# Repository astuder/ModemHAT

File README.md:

# Modem HAT for the Raspberry Pi

This HAT is a modem that connects the Raspberry Pi to a plain old analog telephone line.

The modem presents itself to the Raspberry Pi on an UART and is controlled with the classic AT command set. It supports various standards (V.22bis, V.32bis, V.34, V.90, ...) at speeds of up to 56 kbps.

The design is based on a [Skyworks ISOmodem](https://www.skyworksinc.com/en/Products/Modems-and-DAAs/Data-and-Voice-Modems) chipset, specifically [Si2457](https://www.skyworksinc.com/en/Products/Modems-and-DAAs/Data-and-Voice-Modems/Si2457) data modem and Si3018 line side driver. The implementation
closely follows the circuits described in application note [AN93](https://www.skyworksinc.com/-/media/SkyWorks/SL/documents/public/application-notes/AN93.pdf).

The Modem HAT was successfully tested on the [Shadytel](https://shady.tel/) phone network at Toorcamp 2022.

> [!CAUTION]
> Whatever your jurisdiction, we're pretty positive that connecting this device to the public phone system IS NOT LEGAL! Don't blame us if you get into trouble.

## Raspberry Pi Configuration

> [!NOTE]
> This information was tested on Raspberry Pi 4 and Raspberry 5, running Raspberry Pi OS 12 (Bookworm). There may be differences for other versions of the Pi and/or Pi OS.

The modem HAT requires a Raspberry Pi 4 or newer.

The modem communicates through the Pi's UART on GPIO 8-11, and requires CTS and RTS for flow control. The modem supports automatic baudrate detection at speeds up to 307.2 kps.

Before first use after power-up, the modem needs to be reset. To reset the modem, GPIO25 (pin 22) is set low for at least 500ms, then set high, followed by a delay of at least 300ms. 

By default, the modem is configured for operation in the United States. For other countries the modem may have to be reconfigured after reset. See [AN93](https://www.skyworksinc.com/-/media/SkyWorks/SL/documents/public/application-notes/AN93.pdf) chapter 6.2 for details. 

Below are the configuration steps for Raspberry Pi 4 and Raspberry Pi 5.

### Raspberry Pi 4

To enable the UART, edit `/boot/firmware/config.txt` and add the following line at the end of the file:

`dtoverlay=uart4,ctsrts`

After rebooting the Raspberry Pi, the UART is mapped to `/dev/ttyAMA4`.

To reset the modem, run the Python script [`reset-pi4.py`](python/reset-pi4.py).

The modem is now ready to use. For example connect to the modem by running:

`screen /dev/ttyAMA4 115200`

Once connected to the modem, if you type `at` and press enter, the modem should respond with `OK`.

### Raspberry Pi 5

To enable the UART, edit `/boot/firmware/config.txt` and add the following line at the end of the file:

`dtoverlay=uart3-pi5,ctsrts`

After rebooting the Raspberry Pi, the UART is mapped to `/dev/ttyAMA3`.

To reset the modem, run the Python script [`reset-pi5.py`](python/reset-pi5.py).

The modem is now ready to use. For example connect to the modem by running:

`screen /dev/ttyAMA3 115200`

Once connected to the modem, if you type `at` and press enter, the modem should respond with `OK`.

## AT Command Set

The modem supports the [basic Hayes command set](https://en.wikipedia.org/wiki/Hayes_command_set#The_basic_Hayes_command_set).

For a complete list of supported AT commands as well as configuration registers refer to [AN93](https://www.skyworksinc.com/-/media/SkyWorks/SL/documents/public/application-notes/AN93.pdf) chapters 5.4 through 5.7. 

## Raspberry Pi GPIO Pinout

Required connections:
|Pin|Description|
|-|-|
|1|3.3V power for modem chipset|
|2,4|5V power for audio amplifier|
|6|GND|
|19|UART CTS|
|21|UART RX|
|22|Modem reset, RPi GPIO25|
|23|UART RTS|
|24|UART TX|

Optional connections:
|Pin|Description|
|-|-|
|13|Modem interrupt, RPi GPIO27|
|15|Modem boot config EEPROM SDIO, RPi GPIO22|
|16|Modem boot config EEPROM CS, RPi GPIO23|
|18|Modem boot config EEPROM CLK, Rpi GPIO24|
|27|RPi config EEPROM SDA|
|28|RPi config EEPROM SCL|

In the standard configuration of the HAT, the modem boot config and interrupt pins are not electrically connected to the Rasbperry Pi GPIO header. Populate R29-R32 with 0-ohm resistors to use these pins.

## Building Your Own HAT

### General

Large parts of the HAT are based on the hardware design reference in application note [AN93](https://www.skyworksinc.com/-/media/SkyWorks/SL/documents/public/application-notes/AN93.pdf) chapter 4. Where applicable, identical component designators are used to simplify cross-referencing. 

I used solder paste, stencil and reflow oven for assembly of the HAT. I also ordered partially assembled boards from JLCPCB, and manually soldered the parts that they didn't have in stock (modem chipset and high-voltage capacitors).

After soldering the through-hole parts (RJ11 connector, speaker), make sure to clip the leads on the bottom side of the HAT to avoid shorting with metal parts on the Raspberry Pi.

### Modem

The modem chipset consists of the digital part Si2457 (U1) and analog part Si3018 (U2).

These are expensive parts, costing US $13-$16 and $6-$8 respectively when purchased from reputable distributors. While tempting, beware of sources like Ebay and AliExpress as parts may be salvaged, old or even fake. It will be much easier to diagnose problems without having to second guess whether the core components of the HAT are genuine.

The HAT uses a 32.768 kHz crystal (Y1) to clock the Si2457, mainly chosen for small size and because I already had a few in my parts bin. The downside of this choice are the slow reset sequence (800 ms) and that this clocking option is only supported by Si2457 revision D (part number SI2457-D-FT) or newer.

If you suspect that you're stuck with an old part, you could try using a 4.9152 MHz crystal instead. In that case you must remove R17 which configures the clock speed. You may also have to replace the load capacitors (C40, C41) with appropriate values. See [AN93](https://www.skyworksinc.com/-/media/SkyWorks/SL/documents/public/application-notes/AN93.pdf) chapter 4.1.3 for details.

On the analog side, most of the resistors, capacitors, diodes and transistors have critical voltage, current and/or power ratings. These are all called out in the schematic. See bill of material in [AN93](https://www.skyworksinc.com/-/media/SkyWorks/SL/documents/public/application-notes/AN93.pdf) chapter 4.3 for full details. 

For bring-up and troubleshooting of the modem portion of the circuit, refer to [AN93](https://www.skyworksinc.com/-/media/SkyWorks/SL/documents/public/application-notes/AN93.pdf) chapter 10.1. 

### Audio Output / Speaker

The audio output is optional and allows monitoring of connection progress via a speaker, and who doesn't love the old-school sounds of two dial-up modems negotiating a session. It's half the reason to build this project! :)

The audio amplifier LM4819 (U4) can be substituted with the higher power, pin-compatible LM4862. Cheap, off-brand substitutes are probably fine too.

The HAT has a footprint for a 15mm speaker, like for example CUI Devices CVS-1508. Alternatively, footprint J3 provides connectivity via a JST-PH connector, or directly soldering speaker wires to the pads.

If audio is not needed, the audio amplifier (U4) and associated parts (C12-C19, R19-R24, SW1, J3) can be left unpopulated.

To enable audio output on the speaker, make sure MUTE switch is set towards the LEDs. The AT command to enable speaker output while dialing and handshaking is `ATM1`. Speaker volume is controlled with `ATL1` through `ATL4`, where 4 is the loudest.

### Modem Boot Config EEPROM

The modem boot config EEPROM is optional and can store AT commands that the modem automatically runs after reset. See [AN93](https://www.skyworksinc.com/-/media/SkyWorks/SL/documents/public/application-notes/AN93.pdf) chapter 2.7 for details.

The EEPROM can be programmed by the modem with AT commands. For hacking, the EEPROM can also be connected to the Raspberry Pi by populating R29, R30 and R31. For the latter, keep the modem in reset while interacting with the EEPROM.

If this functionality is not needed, the EEPROM (U6) and associated parts (C22, R26, R27, R28) can be left unpopulated.

### Raspberry Pi HAT ID EEPROM

The HAT ID EEPROM is optional and can store information that allows the Raspberry Pi to recognize the HAT and load the required device tree overlay, i.e. automatically configure UART and other pins.

I haven't figured out the content for this EEPROM yet. Specification is [here](https://github.com/raspberrypi/hats/blob/master/eeprom-format.md). Contributions are welcome :)

If this functionality is not needed, the EEPROM (U5) and associated parts (C21, R14, R25) can be left unpopulated.

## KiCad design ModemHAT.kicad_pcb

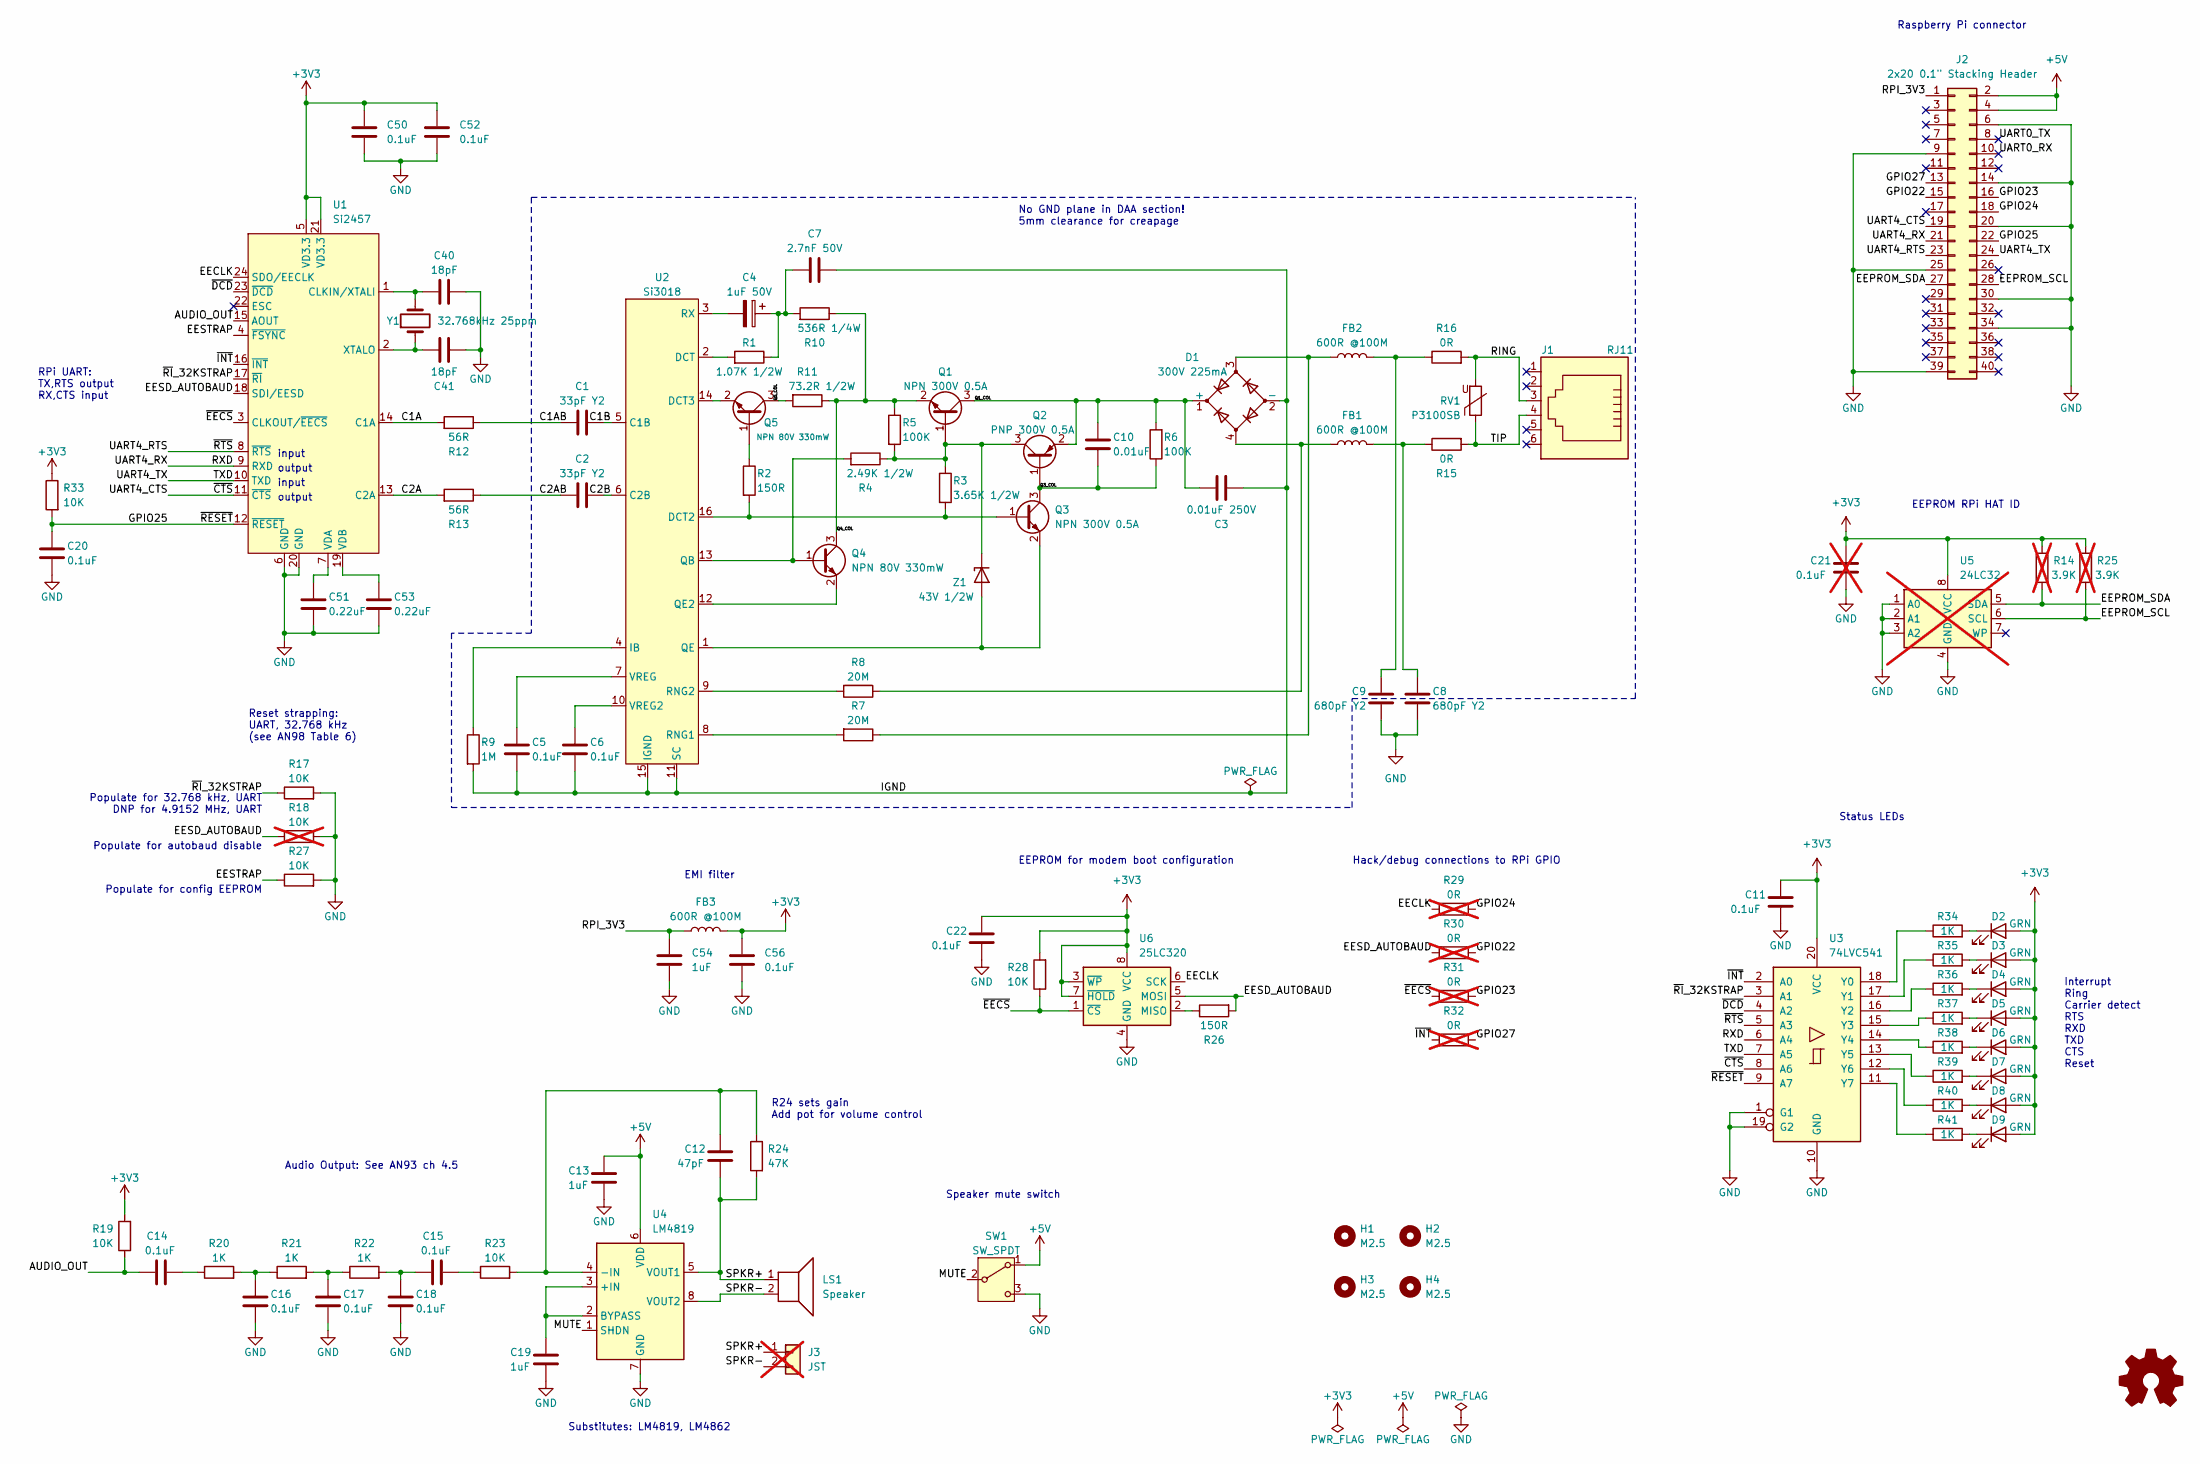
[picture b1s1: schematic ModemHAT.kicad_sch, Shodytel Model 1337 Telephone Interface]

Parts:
C1, C2: 33pF Y2; C_1808_4520Metric; MPN SCC1808N330J502TG
C3: 0.01uF 250V; C_0805_2012Metric; MPN GRM21BR72E103KW03L
C4: 1uF 50V; CP_Elec_4x5.4; LCSC C371267
C5, C6, C11, C14, C15, C16, C17, C18, C20, C22, C50, C52, C56: 0.1uF; C_0603_1608Metric; LCSC C14663
C7: 2.7nF 50V; C_0603_1608Metric; LCSC C1609
C8, C9: 680pF Y2; C_1808_4520Metric; MPN 502R29W681KV3E-****-SC
C10: 0.01uF; C_0603_1608Metric; LCSC C57112
C12: 47pF; C_0603_1608Metric; LCSC C1671
C13, C19, C54: 1uF; C_0603_1608Metric; LCSC C15849
C21: 0.1uF; C_0603_1608Metric; LCSC C14663; not fitted
C40, C41: 18pF; C_0603_1608Metric; LCSC C1647
C51, C53: 0.22uF; C_0603_1608Metric; LCSC C21120
D1: 300V 225mA; TO-269AA-R; MPN MB4S-TP; LCSC C151727
D2, D3, D4, D5, D6, D7, D8, D9: GRN; LED_0805_2012Metric; LCSC C2297
FB1, FB2, FB3: 600R @100M; L_0603_1608Metric; MPN BLM18AG601SN1D; LCSC C1002
H1, H2, H3, H4: M2.5; MountingHole_2.7mm_M2.5
J1: RJ11; RJ12_Amphenol_54601-x06_Horizontal; MPN 54601-906001WPLF
J2: 2x20 0.1" Stacking Header; Raspberry_Pi_Stacking_Header; LCSC C2685112
J3: JST; JST_PH_B2B-PH-K_1x02_P2.00mm_Vertical; not fitted
LS1: Speaker; Buzzer_15x7.5RM7.6; MPN CVS-1508
Q1, Q3: NPN 300V 0.5A; SOT-23; MPN MMBTA42; LCSC C20069138
Q2: PNP 300V 0.5A; SOT-23; MPN MMBTA92; LCSC C20069146
Q4, Q5: NPN 80V 330mW; SOT-323_SC-70; MPN MMBTA06W; LCSC C268584
R1: 1.07K 1/2W; R_1210_3225Metric; LCSC C333114
R2, R26: 150R; R_0603_1608Metric; LCSC C22808
R3: 3.65K 1/2W; R_1210_3225Metric; LCSC C230230
R4: 2.49K 1/2W; R_1210_3225Metric; LCSC C705453
R5, R6: 100K; R_0603_1608Metric; LCSC C25803
R7, R8: 20M; R_1206_3216Metric; LCSC C384452
R9: 1M; R_0603_1608Metric; LCSC C22935
R10: 536R 1/4W; R_1206_3216Metric; LCSC C364152
R11: 73.2R 1/2W; R_1210_3225Metric; LCSC C2991291
R12, R13: 56R; R_0603_1608Metric; LCSC C25196
R14, R25: 3.9K; R_0603_1608Metric; LCSC C23018; not fitted
R15, R16: 0R; R_0603_1608Metric; LCSC C21189
R17, R19, R23, R27, R28, R33: 10K; R_0603_1608Metric; LCSC C25804
R18: 10K; R_0603_1608Metric; LCSC C25804; not fitted
R20, R21, R22, R34, R35, R36, R37, R38, R39, R40, R41: 1K; R_0603_1608Metric; LCSC C21190
R24: 47K; R_0603_1608Metric; LCSC C25819
R29, R30, R31, R32: 0R; R_0603_1608Metric; LCSC C25819; not fitted
RV1: P3100SB; D_SMB; MPN P3100SBLRP; LCSC C3012560
SW1: SW_SPDT; SW_SPDT_CK_JS102011SAQN; MPN JS102011SAQN; LCSC C221660
U1: Si2457; TSSOP-24_4.4x7.8mm_P0.65mm; MPN Si2457-D-FT
U2: Si3018; SOIC-16_3.9x9.9mm_P1.27mm; MPN Si3018-F-GS
U3: 74LVC541; TSSOP-20_4.4x6.5mm_P0.65mm; LCSC C5657
U4: LM4819; SOIC-8_3.9x4.9mm_P1.27mm; MPN LM4819MX/NOPB; LCSC C87265
U5: 24LC32; TSSOP-8_4.4x3mm_P0.65mm; MPN CAT24C32YI-GT3; not fitted
U6: 25LC320; TSSOP-8_4.4x3mm_P0.65mm; MPN 25LC320AT-I/ST; LCSC C2061659
Y1: 32.768kHz 25ppm; Crystal_SMD_3215-2Pin_3.2x1.5mm; MPN ECS-.327-12.5-34B-TR; LCSC C32346
Z1: 43V 1/2W; D_SOD-123; MPN MMSZ5260BT1G; LCSC C6909653

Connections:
+3V3: C11.1, C21.1, C22.1, C50.2, C52.2, C56.2, D2.2 (A), D3.2 (A), D4.2 (A), D5.2 (A), D6.2 (A), D7.2 (A), D8.2 (A), D9.2 (A), FB3.2, R14.1, R19.2, R25.1, R28.2, R33.1, U1.5 (VD3.3), U1.21 (VD3.3), U3.20 (VCC), U5.8 (VCC), U6.3 (~WP), U6.7 (~HOLD), U6.8 (VCC)
+5V: C13.2, J2.2, J2.4, SW1.1 (A), U4.6 (VDD)
/AUDIO_OUT: C14.2, R19.1, U1.15 (AOUT)
/C1A: R12.2, U1.14 (C1A)
/C1AB: C1.1, R12.1
/C1B: C1.2, U2.5 (C1B)
/C2A: R13.2, U1.13 (C2A)
/C2AB: C2.1, R13.1
/C2B: C2.2, U2.6 (C2B)
/EECLK: R29.2, U1.24 (SDO/EECLK), U6.6 (SCK)
/EEPROM_SCL: J2.28, R25.2, U5.6 (SCL)
/EEPROM_SDA: J2.27, R14.2, U5.5 (SDA)
/EESD_AUTOBAUD: R18.1, R26.2, R30.2, U1.18 (SDI/EESD), U6.5 (MOSI)
/EESTRAP: R27.1, U1.4 (~FSYNC)
/GPIO22: J2.15, R30.1
/GPIO23: J2.16, R31.1
/GPIO24: J2.18, R29.1
/GPIO25: C20.2, J2.22, R33.2, U1.12 (~RESET), U3.9 (A7)
/GPIO27: J2.13, R32.1
/IGND: C3.1, C5.2, C6.2, C7.1, D1.2 (-), R9.2, U2.11 (SC), U2.15 (IGND)
/MUTE: SW1.2 (B), U4.1 (SHDN)
/Q1_COL: C3.2, C10.2, D1.1 (+), Q1.3 (C), Q2.2 (E), R6.2
/Q3_COL: C10.1, Q2.1 (B), Q3.3 (C), R6.1
/Q4_COL: Q1.2 (E), Q4.3 (C), R5.1, R10.1, R11.1
/Q5_COL: Q5.3 (C), R11.2
/RING: J1.3, R16.2, RV1.2
/RPI_3V3: C54.2, FB3.1, J2.1
/RXD: J2.21, U1.9 (RXD), U3.6 (A4)
/SPKR+: C12.2, J3.1, LS1.1, R24.2, U4.5 (VOUT1)
/SPKR-: J3.2, LS1.2, U4.8 (VOUT2)
/TIP: J1.4, R15.2, RV1.1
/TXD: J2.24, U1.10 (TXD), U3.7 (A5)
/UART0_RX: J2.10
/UART0_TX: J2.8
/UART4_CTS: J2.19, U1.11 (~CTS), U3.8 (A6)
/UART4_RTS: J2.23, U1.8 (~RTS), U3.5 (A3)
/~DCD: U1.23 (~DCD), U3.4 (A2)
/~EECS: R28.1, R31.2, U1.3 (CLKOUT/~EECS), U6.1 (~CS)
/~INT: R32.2, U1.16 (~INT), U3.2 (A0)
/~RI_32KSTRAP: R17.1, U1.17 (~RI), U3.3 (A1)
GND: C8.2, C9.2, C11.2, C13.1, C16.1, C17.1, C18.1, C19.1, C20.1, C21.2, C22.2, C40.2, C41.2, C50.1, C51.2, C52.1, C53.2, C54.1, C56.1, J2.6, J2.9, J2.14, J2.20, J2.25, J2.30, J2.34, J2.39, R17.2, R18.2, R27.2, SW1.3 (C), U1.6 (GND), U1.20 (GND), U3.1 (G1), U3.10 (GND), U3.19 (G2), U4.7 (GND), U5.1 (A0), U5.2 (A1), U5.3 (A2), U5.4 (GND), U6.4 (GND)
unnamed: C4.1, C7.2, R1.1, R10.2
unnamed: C8.1, FB1.2, R15.1
unnamed: C9.1, FB2.2, R16.1
unnamed: C14.1, R20.1
unnamed: C15.1, R23.1
unnamed: C15.2, C18.2, R22.2
unnamed: C16.2, R20.2, R21.1
unnamed: C17.2, R21.2, R22.1
unnamed: D1.3, FB2.1, R7.1
unnamed: D1.4, FB1.1, R8.1
unnamed: D2.1 (K), R34.2
unnamed: D3.1 (K), R35.2
unnamed: D4.1 (K), R36.2
unnamed: D5.1 (K), R37.2
unnamed: D6.1 (K), R38.2
unnamed: D7.1 (K), R39.2
unnamed: D8.1 (K), R40.2
unnamed: D9.1 (K), R41.2
unnamed: Q1.1 (B), Q2.3 (C), R3.1, R4.1, R5.2, Z1.1 (K)
unnamed: Q3.1 (B), R2.2, R3.2, U2.16 (DCT2)
unnamed: Q3.2 (E), U2.1 (QE), Z1.2 (A)
unnamed: Q4.1 (B), R4.2, U2.13 (QB)
unnamed: Q4.2 (E), U2.12 (QE2)
unnamed: Q5.1 (B), R2.1
unnamed: Q5.2 (E), U2.14 (DCT3)
unnamed: C40.1, U1.1 (CLKIN/XTALI), Y1.2
unnamed: C51.1, U1.7 (VDA)
unnamed: C53.1, U1.19 (VDB)
unnamed: C41.1, U1.2 (XTALO), Y1.1
unnamed: R1.2, U2.2 (DCT)
unnamed: R9.1, U2.4 (IB)
unnamed: R7.2, U2.8 (RNG1)
unnamed: R8.2, U2.9 (RNG2)
unnamed: C4.2, U2.3 (RX)
unnamed: C6.1, U2.10 (VREG2)
unnamed: C5.1, U2.7 (VREG)
unnamed: R34.1, U3.18 (Y0)
unnamed: R35.1, U3.17 (Y1)
unnamed: R36.1, U3.16 (Y2)
unnamed: R37.1, U3.15 (Y3)
unnamed: R38.1, U3.14 (Y4)
unnamed: R39.1, U3.13 (Y5)
unnamed: R40.1, U3.12 (Y6)
unnamed: R41.1, U3.11 (Y7)
unnamed: C19.2, U4.2 (BYPASS), U4.3 (+IN)
unnamed: C12.1, R23.2, R24.1, U4.4 (-IN)
unnamed: R26.1, U6.2 (MISO)

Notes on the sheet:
Audio Output: See AN93 ch 4.5
Reset strapping: UART, 32.768 kHz (see AN98 Table 6)
EEPROM for modem boot configuration
output
Populate for autobaud disable
EMI filter
Interrupt Ring Carrier detect RTS RXD TXD CTS Reset
EEPROM RPi HAT ID
Status LEDs
Populate for 32.768 kHz, UART DNP for 4.9152 MHz, UART
Speaker mute switch
No GND plane in DAA section! 5mm clearance for creapage
Hack/debug connections to RPi GPIO
Populate for config EEPROM
Raspberry Pi connector
R24 sets gain Add pot for volume control
input
Substitutes: LM4819, LM4862
RPi UART: TX,RTS output RX,CTS input

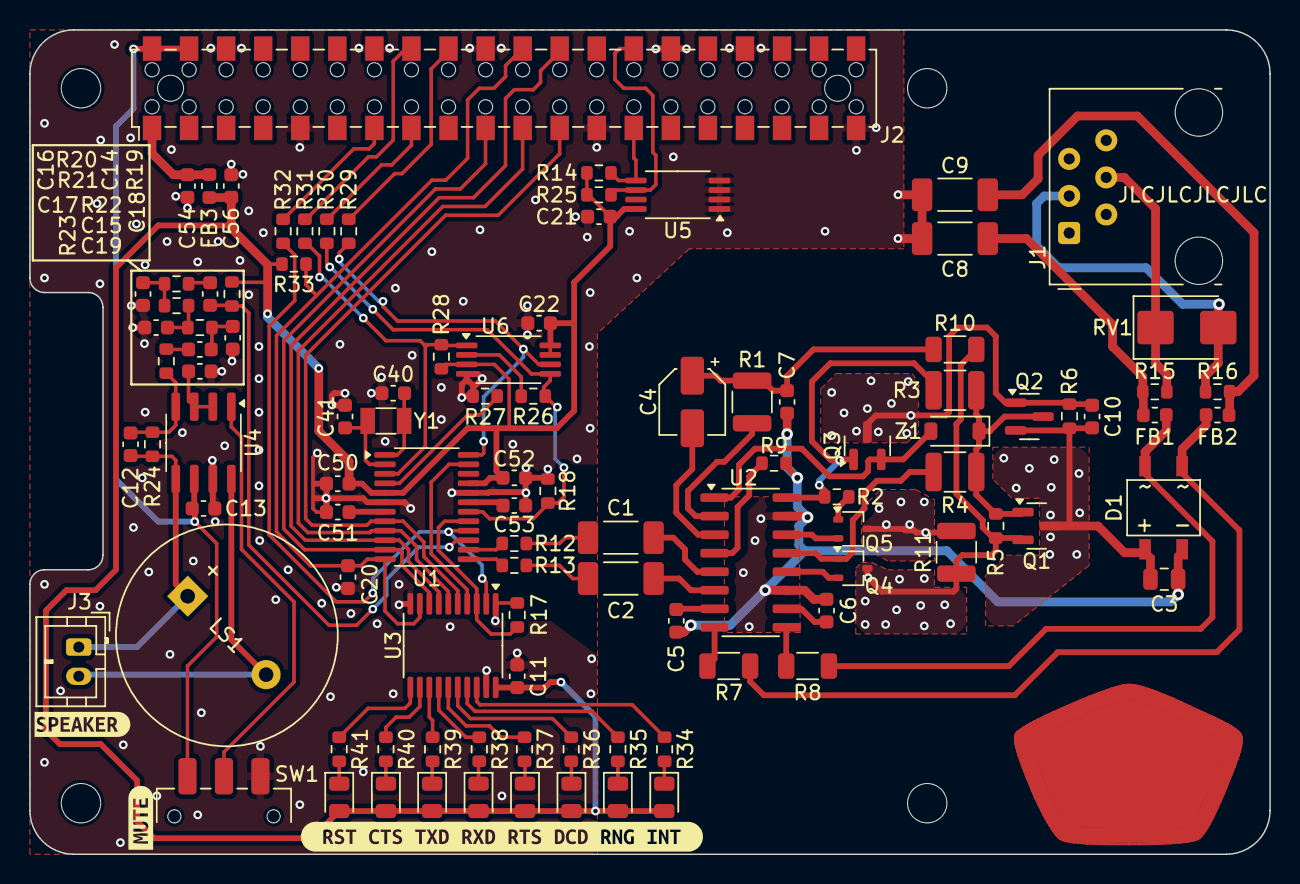
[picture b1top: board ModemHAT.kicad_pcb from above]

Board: 2 copper layers, 85.0 x 56.5 mm, 109 parts (0 on the bottom side), 86 nets.

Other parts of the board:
kibuzzard-665D11B2: G***; kibuzzard-665D11B2
kibuzzard-665D1212: G***; kibuzzard-665D1212
kibuzzard-62720846: G***; kibuzzard-62720846

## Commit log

2022-06-04 project description
2022-06-04 move trace away from mounting hole
2022-06-04 more documentation
2022-06-04 formatting, typos
2022-06-04 minor edits
2022-06-04 move vias
2022-06-04 added more mfg part numbers
2022-06-05 audio circuit comments
2022-06-05 notes for building HAT
2022-06-06 reference to troubleshooting documentation
2022-07-15 add RPi4 compatibility note
2022-07-28 minor PCB edits, report successful field test
2024-06-12 rev B
2024-06-12 update render
2024-06-12 update render url
2024-06-12 update notes about building HAT
2024-06-13 document use with RPi 5
2024-07-01 add schematic PDF

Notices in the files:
ModemHAT.kicad_pcb:
©2022-2024 Adrian Studer
Licensed under CERN-OHL-P-2.0
